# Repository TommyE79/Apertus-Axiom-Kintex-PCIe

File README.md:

# Apertus-Axiom-Kintex-PCIe
 Apertus-Axiom-Kintex-PCIe Bases on SSITLINV-FPGA_Board

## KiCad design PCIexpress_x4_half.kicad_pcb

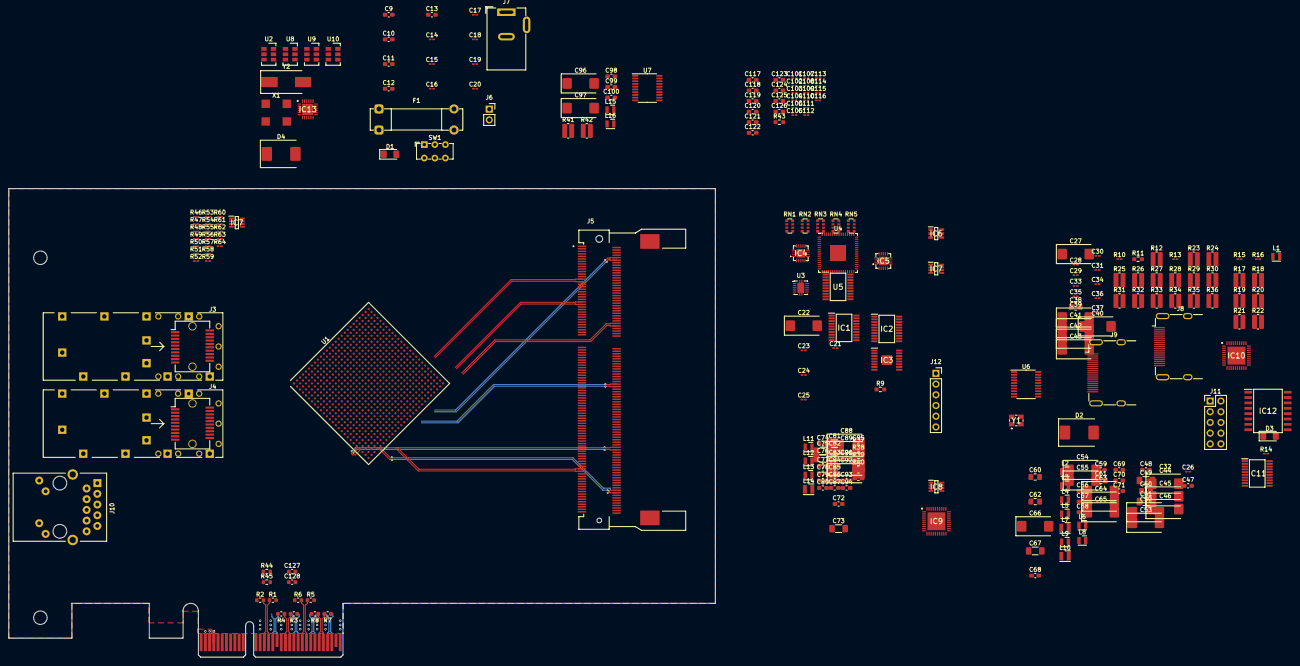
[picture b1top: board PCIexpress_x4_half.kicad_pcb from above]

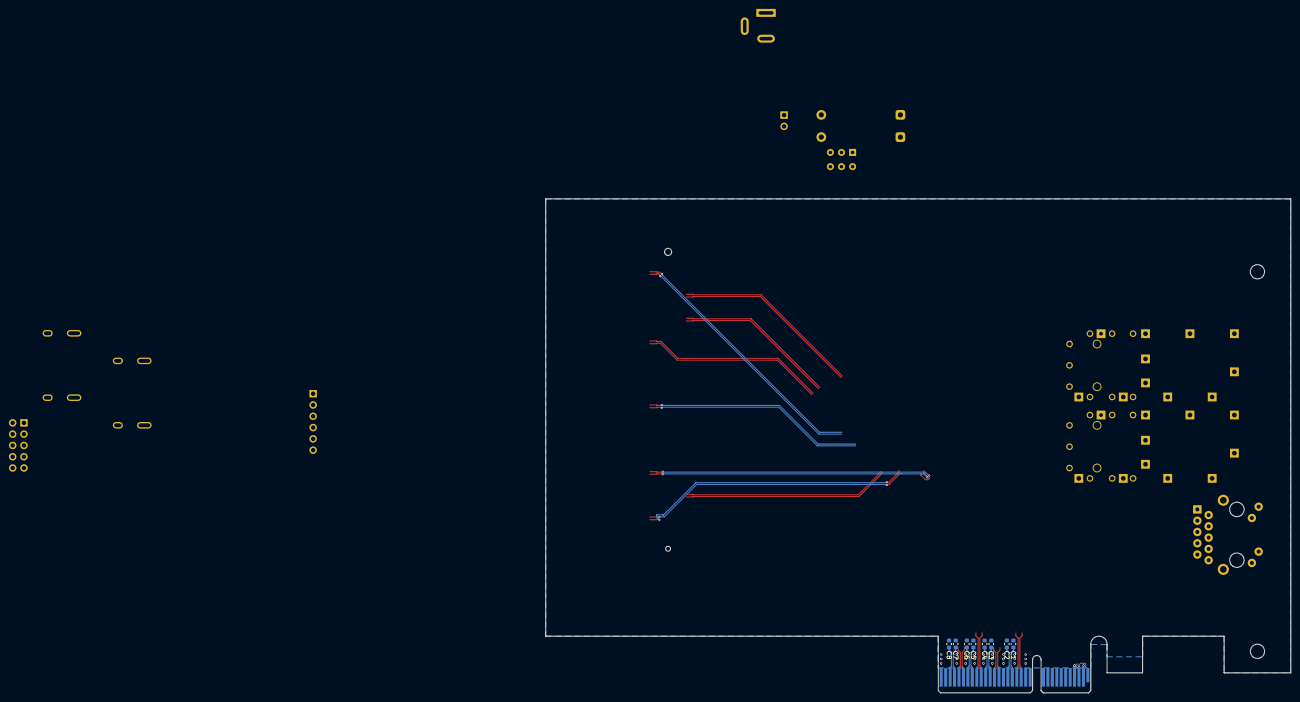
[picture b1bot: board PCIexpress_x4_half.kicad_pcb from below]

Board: 4 copper layers, 167.7 x 111.2 mm, 258 parts (8 on the bottom side), 241 nets.

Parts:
C1, C2, C3, C4, C5, C6, C7, C8, C127, C128: 100n; C_0603_1608Metric
C9, C10, C11, C12, C13, C48, C56, C57, C58, C59, C68, C69, C70, C71, C72, C74, C77, C78, C79, C80, C87, C90, C93, C94, C95, C98, C99, C100, C117, C118, C119, C120, C121, C122, C123, C124, C125, C126: 100n; C_0603_1608Metric_Pad1.08x0.95mm_HandSolder
C14, C15, C16, C17, C18, C19, C20, C21, C23, C24, C25, C26, C28, C29, C30, C31, C32, C33, C34, C35, C36, C37, C101, C102, C103, C104, C105, C106, C107, C108, C109, C110, C111, C112, C113, C114, C115, C116: 100n; C_0201_0603Metric_Pad0.64x0.40mm_HandSolder
C22, C27: 330u; CP_EIA-7343-30_AVX-N_Pad2.25x2.55mm_HandSolder
C38, C50: 100n; C_0805_2012Metric_Pad1.18x1.45mm_HandSolder
C39, C43, C63: 22uF; CP_EIA-7343-40_Kemet-Y_Pad2.25x2.55mm_HandSolder
C40, C41, C42, C44, C45, C46, C64, C65, C66: 22uf; CP_EIA-7343-43_Kemet-X_Pad2.25x2.55mm_HandSolder
C47: 100p; C_0603_1608Metric_Pad1.08x0.95mm_HandSolder
C49, C51: 1u; C_1206_3216Metric_Pad1.33x1.80mm_HandSolder
C52, C53, C54, C55: 330uF; CP_EIA-7343-43_Kemet-X_Pad2.25x2.55mm_HandSolder
C60, C62: 330p; C_0805_2012Metric_Pad1.18x1.45mm_HandSolder
C61: 22p; C_0805_2012Metric_Pad1.18x1.45mm_HandSolder
C67, C73, C75, C81: 10u; C_1206_3216Metric_Pad1.33x1.80mm_HandSolder
C76, C82: 330u; C_1206_3216Metric_Pad1.33x1.80mm_HandSolder
C83, C85: 8200p; C_0603_1608Metric_Pad1.08x0.95mm_HandSolder
C84, C86: 10n; C_0603_1608Metric_Pad1.08x0.95mm_HandSolder
C88, C91: 100u; CP_EIA-7343-43_Kemet-X_Pad2.25x2.55mm_HandSolder
C89, C96: 22u; CP_EIA-7343-43_Kemet-X_Pad2.25x2.55mm_HandSolder
C92: 330u; CP_EIA-7343-43_Kemet-X_Pad2.25x2.55mm_HandSolder
C97: 330u; CP_EIA-7343-31_Kemet-D_Pad2.25x2.55mm_HandSolder
D1, D3: LED; LED_1206_3216Metric_Pad1.42x1.75mm_HandSolder
D2, D4: B340; D_SMC
F1: Fuse; Fuseholder_Clip-5x20mm_Bel_FC-203-22_Lateral_P17.80x5.00mm_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
IC1, IC2, IC11: TXS0108EPWRG4; SOP65P640X120-20N
IC3: TPS40057PWP; SOP65P640X120-17N
IC4, IC5: TPS54620RHLR; TPS54622RHLR
IC6: MP2359DJ-LF-Z; SOT95P280X100-6N
IC7, IC7#2, IC8: MP2315SGJ-Z; SOT65P280X100-8N
IC9, IC10: TMDS141RHAR; QFN50P600X600X100-41N-D
IC12: S25FL256LAGMFI001; SOIC127P1030X265-16N
IC13: SI5338A-B04911-GM; QFN50P400X400X90-25N-D
J1: PCIexpress_x4
J2: PCIexpress_bracket; PCIexpress_bracket_full
J3, J4: SFP+; Connector_SFP_and_Cage
J5: 2-2013289-2; TE_2-2013289-2
J6: FAN; PinSocket_1x02_P2.54mm_Vertical
J7: Jack-DC; BarrelJack_Wuerth_6941xx301002
J8, J9: HDMI_A_1.4; HDMI_A_Molex_208658-1001_Horizontal
J10: RJ45_RB1-125B8G1A; RJ45_UDE_RB1-125B8G1A
J11: Conn_02x05_Odd_Even; PinHeader_2x05_P2.54mm_Vertical
J12: Conn_01x06_Socket; PinSocket_1x06_P2.54mm_Vertical
L1, L2: 100n; L_Wurth_WE-LQSH-2010
L3, L4, L5, L6: L; L_Wurth_WE-LQSH-2010
L7: 1u5; L_Wurth_WE-LQSH-2512
L8, L9, L11, L12, L13, L15, L16: 100nH; L_Wurth_WE-LQSH-2010
L10, L14: 3u3; L_Wurth_WE-LQSH-2512
R1, R2, R3, R4, R5, R6, R7, R8, R44, R45: 49.9; R_0603_1608Metric
R9, R43: 49R9; R_0603_1608Metric_Pad0.98x0.95mm_HandSolder
R10: 49R9; R_0201_0603Metric_Pad0.64x0.40mm_HandSolder
R11: 4k7; R_0603_1608Metric_Pad0.98x0.95mm_HandSolder
R12, R37, R41: R; R_0612_1632Metric_Pad1.18x3.40mm_HandSolder
R13, R14, R15, R16: 4k7; R_0201_0603Metric_Pad0.64x0.40mm_HandSolder
R17: 20k; R_0612_1632Metric_Pad1.18x3.40mm_HandSolder
R18: 59k; R_0612_1632Metric_Pad1.18x3.40mm_HandSolder
R19: 120k; R_0612_1632Metric_Pad1.18x3.40mm_HandSolder
R20: 1k; R_0612_1632Metric_Pad1.18x3.40mm_HandSolder
R21, R22, R35, R39: 100k; R_0612_1632Metric_Pad1.18x3.40mm_HandSolder
R23: 10k; R_0612_1632Metric_Pad1.18x3.40mm_HandSolder
R24: 43k2; R_0612_1632Metric_Pad1.18x3.40mm_HandSolder
R25, R26, R27, R28: 4k7; R_0612_1632Metric_Pad1.18x3.40mm_HandSolder
R29, R32: 1k69; R_0612_1632Metric_Pad1.18x3.40mm_HandSolder
R30, R33: 24k; R_0612_1632Metric_Pad1.18x3.40mm_HandSolder
R31, R34: 22k; R_0612_1632Metric_Pad1.18x3.40mm_HandSolder
R36, R40: 35k7; R_0612_1632Metric_Pad1.18x3.40mm_HandSolder
R38, R42: 8k06; R_0612_1632Metric_Pad1.18x3.40mm_HandSolder
R46: 27k; R_0201_0603Metric_Pad0.64x0.40mm_HandSolder
R47: 60k4; R_0201_0603Metric_Pad0.64x0.40mm_HandSolder
R48, R55: 40k2; R_0201_0603Metric_Pad0.64x0.40mm_HandSolder
R49: 49k9; R_0201_0603Metric_Pad0.64x0.40mm_HandSolder
R50, R52, R64: 100k; R_0201_0603Metric_Pad0.64x0.40mm_HandSolder
R51, R62: 10R; R_0201_0603Metric_Pad0.64x0.40mm_HandSolder
R53: 59k; R_0201_0603Metric_Pad0.64x0.40mm_HandSolder
R54, R63: 0R; R_0201_0603Metric_Pad0.64x0.40mm_HandSolder
R56: 31k6; R_0201_0603Metric_Pad0.64x0.40mm_HandSolder
R57: 53k6; R_0201_0603Metric_Pad0.64x0.40mm_HandSolder
R58: 47k; R_0201_0603Metric_Pad0.64x0.40mm_HandSolder
R59: 75k; R_0201_0603Metric_Pad0.64x0.40mm_HandSolder
R60: 20k5; R_0201_0603Metric_Pad0.64x0.40mm_HandSolder
R61: 39k2; R_0201_0603Metric_Pad0.64x0.40mm_HandSolder
RN1, RN2, RN3, RN4, RN5: R_Pack04; R_Array_Convex_4x0612
SW1: SW_SPDT; SW_E-Switch_EG1271_SPDT
U1: XC7K325T-FFG676; Xilinx_FFG676
U2, U8, U9, U10: XUX53; Oscillator_SMD_IDT_JS6-6_5.0x3.2mm_P1.27mm
U3: TPS51200DRC; VSON-10-1EP_3x3mm_P0.5mm_EP1.65x2.4mm
U4: RTL8211EG-VB-CG; QFN-64-1EP_9x9mm_P0.5mm_EP3.8x3.8mm
U5: SN74LV245ATPWR; SOP65P640X120-20N
U6, U7: TXS0108EPW; TSSOP-20_4.4x6.5mm_P0.65mm
X1: XO91; Oscillator_SMD_EuroQuartz_XO91-4Pin_7.0x5.0mm
Y1: X32-25.000-12-30_30_4085; X32250001230304085
Y2: 25M; Crystal_SMD_EuroQuartz_MQ2-2Pin_7.0x5.0mm_HandSoldering

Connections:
+3.3V: J5.199, L8.1, R11.2
+3V3: J1.A9 (+3.3V), J1.A10 (+3.3V), J1.B8 (+3.3V)
+12V: C9.2, C10.2, C11.1, C12.2, C13.2, C14.2, C15.2, C16.2, C17.2, C18.2, C19.2, C20.2, C21.2, C22.2, C23.2, C24.2, C25.2, C26.2, C27.2, C28.2, C29.2, C30.2, C31.2, C32.2, C33.2, C34.2, C35.2, C36.2, C37.2, C38.1, C38.2, C39.1, C39.2, C40.1, C40.2, C41.1, C41.2, C42.1, C42.2, C43.1, C43.2, C44.1, C44.2, C45.1, C45.2, C46.1, C46.2, C47.1, C49.1, C50.1, C52.2, C53.2, C54.2, C55.2, C56.2, C57.2, C58.2, C59.2, C63.2, C64.2, C65.2, C66.2, C67.1, C68.1, C71.1, C83.2, C84.2, C85.2, C86.2, C88.2, C89.1, C89.2, C91.2, C92.2, C93.2, C94.2, C95.2, C96.1, C96.2, C97.2, C98.2, C99.2, C100.2, C101.2, C102.2, C103.2, C104.2, C105.2, C106.2, C107.2, C108.2, C109.2, C110.2, C111.2, C112.2, C113.2, C114.2, C115.2, C116.2, C117.2, C118.2, C119.2, C120.2, C121.2, C122.2, C123.2, C124.2, C125.2, C126.2, F1.2, IC3.5 (SGND), IC3.15 (VIN), IC3.17 (EP), IC4.2 (GND_1), IC4.3 (GND_2), IC4.4 (PVIN_1), IC4.5 (PVIN_2), IC4.6 (VIN), IC4.15 (EP), IC5.2 (GND_1), IC5.3 (GND_2), IC5.4 (PVIN_1), IC5.5 (PVIN_2), IC5.6 (VIN), IC5.15 (EP), IC6.2 (GND), IC7#2.2 (IN), IC7#2.4 (GND), IC8.2 (IN), IC8.4 (GND), J1.A2 (+12V), J1.A3 (+12V), J1.A4 (GND), J1.A12 (GND), J1.A15 (GND), J1.A18 (GND), J1.A20 (GND), J1.A23 (GND), J1.A24 (GND), J1.A27 (GND), J1.A28 (GND), J1.A31 (GND), J1.B1 (+12V), J1.B2 (+12V), J1.B3 (+12V), J1.B4 (GND), J1.B7 (GND), J1.B13 (GND), J1.B16 (GND), J1.B18 (GND), J1.B21 (GND), J1.B22 (GND), J1.B25 (GND), J1.B26 (GND), J1.B29 (GND), J1.B32 (GND), J5.2, J5.3, J5.8, J5.9, J5.13, J5.14, J5.19, J5.20, J5.25, J5.26, J5.31, J5.32, J5.37, J5.38, J5.43, J5.44, J5.48, J5.49, J5.54, J5.55, J5.60, J5.61, J5.65, J5.66, J5.71, J5.72, J5.127, J5.128, J5.133, J5.134, J5.138, J5.139, J5.144, J5.145, J5.150, J5.151, J5.155, J5.156, J5.161, J5.162, J5.167, J5.168, J5.172, J5.173, J5.178, J5.179, J5.184, J5.185, J5.189, J5.190, J5.195, J5.196, J5.197, J5.201, J5.203, J5.204, J5.SH1 (SHIELD), J5.SH2 (SHIELD__1), J6.1, J6.2, J7.2, J7.3, R1.2, R2.2, R3.2, R4.2, R5.2, R6.2, R7.2, R8.2, R10.2, R14.1, R15.1, R16.1, R17.2, R18.1, R19.1, R20.1, R22.1, R26.1, R30.1, R33.1, R35.1, R36.1, R38.2, R39.1, R40.1, R42.2, R44.2, R45.2, R46.2, R47.2, R48.2, R52.1, R56.2, R57.1, R58.1, R61.2, R64.1, U1.A1 (GND), U1.A2 (GND), U1.A5 (GND), U1.A6 (GND), U1.A7 (GND), U1.A16 (GND), U1.A26 (GND), U1.AA6 (GND), U1.AA16 (GND), U1.AA26 (GND), U1.AB3 (GND), U1.AB13 (GND), U1.AB23 (GND), U1.AC10 (GND), U1.AC20 (GND), U1.AD7 (GND), U1.AD17 (GND), U1.AE4 (GND), U1.AE14 (GND), U1.AE24 (GND), U1.AF1 (GND), U1.AF11 (GND), U1.AF21 (GND), U1.B4 (GND), U1.B7 (GND), U1.B13 (GND), U1.B23 (GND), U1.C1 (GND), U1.C5 (GND), U1.C7 (GND), U1.C10 (GND), U1.C20 (GND), U1.D4 (GND), U1.D7 (GND), U1.D17 (GND), U1.E1 (GND), U1.E2 (GND), U1.E5 (GND), U1.E7 (GND), U1.E14 (GND), U1.E24 (GND), U1.F3 (GND), U1.F4 (GND), U1.F7 (GND), U1.F11 (GND), U1.F21 (GND), U1.G1 (GND), U1.G5 (GND), U1.G8 (GND), U1.G18 (GND), U1.H4 (GND), U1.H7 (GND), U1.H15 (GND), U1.H25 (GND), U1.J1 (GND), U1.J2 (GND), U1.J5 (GND), U1.J12 (GND), U1.J22 (GND), U1.K3 (GND), U1.K4 (GND), U1.K7 (GND), U1.K9 (GND), U1.K11 (GND), U1.K13 (GND), U1.K19 (GND), U1.L1 (GND), U1.L5 (GND), U1.L10 (GND), U1.L12 (GND), U1.L14 (GND), U1.L16 (GND), U1.L26 (GND), U1.M4 (GND), U1.M7 (GND), U1.M9 (GND), U1.M13 (GND), U1.M15 (GND), U1.M23 (GND), U1.N1 (GND), U1.N2 (GND), U1.N5 (GND), U1.N7 (GND), U1.N10 (GND), U1.N14 (GND), U1.N20 (GND), U1.P3 (GND), U1.P4 (GND), U1.P9 (GND), U1.P13 (GND), U1.P15 (GND), U1.P17 (GND), U1.R1 (GND), U1.R2 (GND), U1.R5 (GND), U1.R8 (GND), U1.R10 (GND), U1.R14 (GND), U1.R24 (GND), U1.T1 (GND), U1.T3 (GND), U1.T4 (GND), U1.T9 (GND), U1.T11 (GND), U1.T13 (GND), U1.T15 (GND), U1.T21 (GND), U1.U8 (GND), U1.U10 (GND), U1.U12 (GND), U1.U14 (GND), U1.U18 (GND), U1.V5 (GND), U1.V15 (GND), U1.V25 (GND), U1.W2 (GND), U1.W12 (GND), U1.W22 (GND), U1.Y9 (GND), U1.Y19 (GND), U3.4 (GND), U3.8 (GND), U3.11 (GND)
/FPGA - kintex/Bank-B/VCCIO: U1.A21 (VCCO_14), U1.B18 (VCCO_15), U1.C25 (VCCO_14), U1.D22 (VCCO_14), U1.E19 (VCCO_15), U1.F16 (VCCO_15), U1.F26 (VCCO_14), U1.G23 (VCCO_14), U1.H20 (VCCO_15), U1.J17 (VCCO_15), U1.L21 (VCCO_14), U1.M18 (VCCO_15)
/FPGA - kintex/Bank-C/0V75-VREF2: C9.1, C10.1, L1.2, U1.AE16 (IO_L6N_T0_VREF_32), U1.Y18 (IO_L19N_T3_VREF_32)
/FPGA - kintex/Bank-C/DDR1V5: U1.AB18 (VCCO_32), U1.AC15 (VCCO_32), U1.AE19 (VCCO_32), U1.AF16 (VCCO_32), U1.W17 (VCCO_32), U1.Y14 (VCCO_32)
/FPGA - kintex/Bank-C/DDR3-B-EVENT: J5.198, U1.V7 (IO_L2N_T0_33)
/FPGA - kintex/Bank-C/DDR3-B_BA0: J5.109, U1.AE8 (IO_L22P_T3_33)
/FPGA - kintex/Bank-C/DDR3-B_BA1: J5.108, U1.AA7 (IO_L8N_T1_33)
/FPGA - kintex/Bank-C/DDR3-B_BA2: J5.79, U1.AF13 (IO_L23N_T3_33)
/FPGA - kintex/Bank-C/DDR3-B_CKE0: J5.73, U1.AB10 (IO_L14N_T2_SRCC_33)
/FPGA - kintex/Bank-C/DDR3-B_CKE1: J5.74, U1.AA10 (IO_L14P_T2_SRCC_33)
/FPGA - kintex/Bank-C/DDR3-B_CLK0+: J5.101, U1.AC9 (IO_L12P_T1_MRCC_33)
/FPGA - kintex/Bank-C/DDR3-B_CLK0-: J5.103, U1.AD9 (IO_L12N_T1_MRCC_33)
/FPGA - kintex/Bank-C/DDR3-B_CLK1+: J5.102, U1.AA9 (IO_L11P_T1_SRCC_33)
/FPGA - kintex/Bank-C/DDR3-B_CLK1-: J5.104, U1.AB9 (IO_L11N_T1_SRCC_33)
/FPGA - kintex/Bank-C/DDR3-B_CS0: J5.114, U1.AA13 (IO_L16P_T2_33)
/FPGA - kintex/Bank-C/DDR3-B_CS1: J5.121, U1.AD13 (IO_L17N_T2_33)
/FPGA - kintex/Bank-C/DDR3-B_DM0: J5.11, U1.AD16 (IO_L6P_T0_32)
/FPGA - kintex/Bank-C/DDR3-B_DM1: J5.28, U1.AB16 (IO_L12P_T1_MRCC_32)
/FPGA - kintex/Bank-C/DDR3-B_DM2: J5.46, U1.AB19 (IO_L18P_T2_32)
/FPGA - kintex/Bank-C/DDR3-B_DM3: J5.63, U1.V17 (IO_L20N_T3_32)
/FPGA - kintex/Bank-C/DDR3-B_DM4: J5.136, U1.U1 (IO_L2N_T0_34)
/FPGA - kintex/Bank-C/DDR3-B_DM5: J5.153, U1.AA3 (IO_L12P_T1_MRCC_34)
/FPGA - kintex/Bank-C/DDR3-B_DM6: J5.170, U1.AD6 (IO_L18P_T2_34)
/FPGA - kintex/Bank-C/DDR3-B_DM7: J5.187, U1.AE1 (IO_L20N_T3_34)
/FPGA - kintex/Bank-C/DDR3-B_DQ0: J5.5, U1.AF17 (IO_L1N_T0_32)
/FPGA - kintex/Bank-C/DDR3-B_DQ1: J5.7, U1.AE17 (IO_L1P_T0_32)
/FPGA - kintex/Bank-C/DDR3-B_DQ2: J5.15, U1.AF15 (IO_L2N_T0_32)
/FPGA - kintex/Bank-C/DDR3-B_DQ3: J5.17, U1.AF14 (IO_L2P_T0_32)
/FPGA - kintex/Bank-C/DDR3-B_DQ4: J5.4, U1.AE15 (IO_L4N_T0_32)
/FPGA - kintex/Bank-C/DDR3-B_DQ5: J5.6, U1.AD15 (IO_L4P_T0_32)
/FPGA - kintex/Bank-C/DDR3-B_DQ6: J5.16, U1.AF20 (IO_L5N_T0_32)
/FPGA - kintex/Bank-C/DDR3-B_DQ7: J5.18, U1.AF19 (IO_L5P_T0_32)
/FPGA - kintex/Bank-C/DDR3-B_DQ8: J5.21, U1.AA15 (IO_L7N_T1_32)
/FPGA - kintex/Bank-C/DDR3-B_DQ9: J5.23, U1.AA14 (IO_L7P_T1_32)
/FPGA - kintex/Bank-C/DDR3-B_DQ10: J5.33, U1.AC14 (IO_L8P_T1_32)
/FPGA - kintex/Bank-C/DDR3-B_DQ11: J5.35, U1.AD14 (IO_L8N_T1_32)
/FPGA - kintex/Bank-C/DDR3-B_DQ12: J5.22, U1.AB14 (IO_L10P_T1_32)
/FPGA - kintex/Bank-C/DDR3-B_DQ13: J5.24, U1.AB15 (IO_L10N_T1_32)
/FPGA - kintex/Bank-C/DDR3-B_DQ14: J5.34, U1.AA18 (IO_L11N_T1_SRCC_32)
/FPGA - kintex/Bank-C/DDR3-B_DQ15: J5.36, U1.AA17 (IO_L11P_T1_SRCC_32)
/FPGA - kintex/Bank-C/DDR3-B_DQ16: J5.39, U1.AC18 (IO_L13P_T2_MRCC_32)
/FPGA - kintex/Bank-C/DDR3-B_DQ17: J5.41, U1.AD18 (IO_L13N_T2_MRCC_32)
/FPGA - kintex/Bank-C/DDR3-B_DQ18: J5.51, U1.AC17 (IO_L14N_T2_SRCC_32)
/FPGA - kintex/Bank-C/DDR3-B_DQ19: J5.53, U1.AB17 (IO_L14P_T2_SRCC_32)
/FPGA - kintex/Bank-C/DDR3-B_DQ20: J5.40, U1.AA20 (IO_L16N_T2_32)
/FPGA - kintex/Bank-C/DDR3-B_DQ21: J5.42, U1.AA19 (IO_L16P_T2_32)
/FPGA - kintex/Bank-C/DDR3-B_DQ22: J5.50, U1.AD19 (IO_L17N_T2_32)
/FPGA - kintex/Bank-C/DDR3-B_DQ23: J5.52, U1.AC19 (IO_L17P_T2_32)
/FPGA - kintex/Bank-C/DDR3-B_DQ24: J5.57, U1.W14 (IO_L24N_T3_32)
/FPGA - kintex/Bank-C/DDR3-B_DQ25: J5.59, U1.V14 (IO_L24P_T3_32)
/FPGA - kintex/Bank-C/DDR3-B_DQ26: J5.67, U1.V19 (IO_L23N_T3_32)
/FPGA - kintex/Bank-C/DDR3-B_DQ27: J5.69, U1.V18 (IO_L23P_T3_32)
/FPGA - kintex/Bank-C/DDR3-B_DQ28: J5.56, U1.V16 (IO_L20P_T3_32)
/FPGA - kintex/Bank-C/DDR3-B_DQ29: J5.58, U1.W15 (IO_L22P_T3_32)
/FPGA - kintex/Bank-C/DDR3-B_DQ30: J5.68, U1.W16 (IO_L22N_T3_32)
/FPGA - kintex/Bank-C/DDR3-B_DQ31: J5.70, U1.Y17 (IO_L19P_T3_32)
/FPGA - kintex/Bank-C/DDR3-B_DQ32: J5.129, U1.V4 (IO_L6P_T0_34)
/FPGA - kintex/Bank-C/DDR3-B_DQ33: J5.131, U1.U6 (IO_L1P_T0_34)
/FPGA - kintex/Bank-C/DDR3-B_DQ34: J5.141, U1.U5 (IO_L1N_T0_34)
/FPGA - kintex/Bank-C/DDR3-B_DQ35: J5.143, U1.U2 (IO_L2P_T0_34)
/FPGA - kintex/Bank-C/DDR3-B_DQ36: J5.130, U1.V3 (IO_L4P_T0_34)
/FPGA - kintex/Bank-C/DDR3-B_DQ37: J5.132, U1.W3 (IO_L4N_T0_34)
/FPGA - kintex/Bank-C/DDR3-B_DQ38: J5.140, U1.U7 (IO_L5P_T0_34)
/FPGA - kintex/Bank-C/DDR3-B_DQ39: J5.142, U1.V6 (IO_L5N_T0_34)
/FPGA - kintex/Bank-C/DDR3-B_DQ40: J5.147, U1.Y3 (IO_L7P_T1_34)
/FPGA - kintex/Bank-C/DDR3-B_DQ41: J5.149, U1.Y2 (IO_L7N_T1_34)
/FPGA - kintex/Bank-C/DDR3-B_DQ42: J5.157, U1.V2 (IO_L8P_T1_34)
/FPGA - kintex/Bank-C/DDR3-B_DQ43: J5.159, U1.V1 (IO_L8N_T1_34)
/FPGA - kintex/Bank-C/DDR3-B_DQ44: J5.146, U1.W1 (IO_L10P_T1_34)
/FPGA - kintex/Bank-C/DDR3-B_DQ45: J5.148, U1.Y1 (IO_L10N_T1_34)
/FPGA - kintex/Bank-C/DDR3-B_DQ46: J5.158, U1.AB2 (IO_L11P_T1_SRCC_34)
/FPGA - kintex/Bank-C/DDR3-B_DQ47: J5.160, U1.AC2 (IO_L11N_T1_SRCC_34)
/FPGA - kintex/Bank-C/DDR3-B_DQ48: J5.163, U1.AA4 (IO_L13P_T2_MRCC_34)
/FPGA - kintex/Bank-C/DDR3-B_DQ49: J5.165, U1.AB4 (IO_L13N_T2_MRCC_34)
/FPGA - kintex/Bank-C/DDR3-B_DQ50: J5.175, U1.AC4 (IO_L14P_T2_SRCC_34)
/FPGA - kintex/Bank-C/DDR3-B_DQ51: J5.177, U1.AC3 (IO_L14N_T2_SRCC_34)
/FPGA - kintex/Bank-C/DDR3-B_DQ52: J5.164, U1.AC6 (IO_L16N_T2_34)
/FPGA - kintex/Bank-C/DDR3-B_DQ53: J5.166, U1.AB6 (IO_L16P_T2_34)
/FPGA - kintex/Bank-C/DDR3-B_DQ54: J5.174, U1.Y6 (IO_L17P_T2_34)
/FPGA - kintex/Bank-C/DDR3-B_DQ55: J5.176, U1.Y5 (IO_L17N_T2_34)
/FPGA - kintex/Bank-C/DDR3-B_DQ56: J5.181, U1.AD4 (IO_L19P_T3_34)
/FPGA - kintex/Bank-C/DDR3-B_DQ57: J5.183, U1.AD1 (IO_L20P_T3_34)
/FPGA - kintex/Bank-C/DDR3-B_DQ58: J5.191, U1.AF2 (IO_L24N_T3_34)
/FPGA - kintex/Bank-C/DDR3-B_DQ59: J5.193, U1.AE2 (IO_L22N_T3_34)
/FPGA - kintex/Bank-C/DDR3-B_DQ60: J5.180, U1.AE6 (IO_L23P_T3_34)
/FPGA - kintex/Bank-C/DDR3-B_DQ61: J5.182, U1.AE5 (IO_L23N_T3_34)
/FPGA - kintex/Bank-C/DDR3-B_DQ62: J5.192, U1.AF3 (IO_L24P_T3_34)
/FPGA - kintex/Bank-C/DDR3-B_DQ63: J5.194, U1.AE3 (IO_L22P_T3_34)
/FPGA - kintex/Bank-C/DDR3-B_DQS0+: J5.12, U1.AE18 (IO_L3P_T0_DQS_32)
/FPGA - kintex/Bank-C/DDR3-B_DQS0-: J5.10, U1.AF18 (IO_L3N_T0_DQS_32)
/FPGA - kintex/Bank-C/DDR3-B_DQS1+: J5.29, U1.Y15 (IO_L9P_T1_DQS_32)
/FPGA - kintex/Bank-C/DDR3-B_DQS1-: J5.27, U1.Y16 (IO_L9N_T1_DQS_32)
/FPGA - kintex/Bank-C/DDR3-B_DQS2+: J5.47, U1.AD20 (IO_L15P_T2_DQS_32)
/FPGA - kintex/Bank-C/DDR3-B_DQS2-: J5.45, U1.AE20 (IO_L15N_T2_DQS_32)
/FPGA - kintex/Bank-C/DDR3-B_DQS3+: J5.64, U1.W18 (IO_L21P_T3_DQS_32)
/FPGA - kintex/Bank-C/DDR3-B_DQS3-: J5.62, U1.W19 (IO_L21N_T3_DQS_32)
/FPGA - kintex/Bank-C/DDR3-B_DQS4+: J5.137, U1.W6 (IO_L3P_T0_DQS_34)
/FPGA - kintex/Bank-C/DDR3-B_DQS4-: J5.135, U1.W5 (IO_L3N_T0_DQS_34)
/FPGA - kintex/Bank-C/DDR3-B_DQS5+: J5.154, U1.AB1 (IO_L9P_T1_DQS_34)
/FPGA - kintex/Bank-C/DDR3-B_DQS5-: J5.152, U1.AC1 (IO_L9N_T1_DQS_34)
/FPGA - kintex/Bank-C/DDR3-B_DQS6+: J5.171, U1.AA5 (IO_L15P_T2_DQS_34)
/FPGA - kintex/Bank-C/DDR3-B_DQS6-: J5.169, U1.AB5 (IO_L15N_T2_DQS_34)
/FPGA - kintex/Bank-C/DDR3-B_DQS7+: J5.188, U1.AF5 (IO_L21P_T3_DQS_34)
/FPGA - kintex/Bank-C/DDR3-B_DQS7-: J5.186, U1.AF4 (IO_L21N_T3_DQS_34)
/FPGA - kintex/Bank-C/DDR3-B_ODT0: J5.116, U1.AA12 (IO_L16N_T2_33)
/FPGA - kintex/Bank-C/DDR3-B_ODT1: J5.120, U1.Y13 (IO_L18P_T2_33)
/FPGA - kintex/Bank-C/DDR3-B_RAS: J5.110, U1.Y7 (IO_L4N_T0_33)
/FPGA - kintex/Bank-C/DDR3-B_RESET: J5.30, U1.AB20 (IO_L18N_T2_32)
/FPGA - kintex/Bank-C/DDR3-B_SCL: J5.202, U1.W8 (IO_L6N_T0_VREF_33)
/FPGA - kintex/Bank-C/DDR3-B_SDA: J5.200, U1.V8 (IO_L2P_T0_33)
/FPGA - kintex/Bank-C/DDR3-B_WE: J5.113, U1.AF8 (IO_L22N_T3_33)
/FPGA - kintex/Bank-D/0V75-VREF1: C12.1, C13.1, L2.2, U1.AD3 (IO_L19N_T3_VREF_34), U1.W4 (IO_L6N_T0_VREF_34)
/FPGA - kintex/Bank-D/DDR1V5: R9.1, U1.AA1 (VCCO_34), U1.AA11 (VCCO_33), U1.AB8 (VCCO_33), U1.AC5 (VCCO_34), U1.AD2 (VCCO_34), U1.AD12 (VCCO_33), U1.AE9 (VCCO_33), U1.AF6 (VCCO_34), U1.U3 (VCCO_34), U1.V10 (VCCO_33), U1.W7 (VCCO_33), U1.Y4 (VCCO_34)
/FPGA - kintex/Bank-E/PCIE_CLK+: C127.2, U1.H6 (MGTREFCLK0P_115)
/FPGA - kintex/Bank-E/PCIE_CLK-: C128.1, U1.H5 (MGTREFCLK0N_115)
/FPGA - kintex/Bank-F/AVTT1V2: C123.1, C124.1, C125.1, C126.1, R43.2, U1.B3 (MGTAVTT), U1.C2 (MGTAVTT), U1.D3 (MGTAVTT), U1.G2 (MGTAVTT), U1.H3 (MGTAVTT), U1.L2 (MGTAVTT), U1.M3 (MGTAVTT), U1.M5 (MGTAVTTRCAL_115)
/FPGA - kintex/Bank-F/VCCINT1V: C101.1, C102.1, C103.1, C104.1, C105.1, C106.1, C107.1, C108.1, C109.1, C110.1, C111.1, C112.1, C113.1, C114.1, C115.1, C116.1, U1.C6 (MGTAVCC), U1.E6 (MGTAVCC), U1.G6 (MGTAVCC), U1.J6 (MGTAVCC), U1.L6 (MGTAVCC)
/FPGA - kintex/Bank-H/1V8: C117.1, C118.1, C119.1, C120.1, C121.1, C122.1, U1.E8 (VCCBATT_0), U1.L11 (VCCAUX), U1.M10 (VCCAUX), U1.M11 (GNDADC_0), U1.M12 (VCCADC_0), U1.P8 (VCCAUX_IO_G0), U1.P10 (VCCAUX), U1.R9 (VCCAUX_IO_G0), U1.T8 (VCCAUX_IO_G0), U1.T10 (VCCAUX), U1.U11 (VCCAUX)
/FPGA - kintex/Bank-H/VCCINT1V: U1.N13 (VCCBRAM), U1.R13 (VCCBRAM), U1.T12 (VCCBRAM), U1.U13 (VCCBRAM)
/FPGA - kintex/Bank-a/VCCIO: U1.AA21 (VCCO_12), U1.AC25 (VCCO_12), U1.AD22 (VCCO_12), U1.AF26 (VCCO_12), U1.K24 (VCCO_13), U1.N25 (VCCO_13), U1.P22 (VCCO_13), U1.R19 (VCCO_13), U1.T16 (VCCO_13), U1.T26 (VCCO_13), U1.U23 (VCCO_12), U1.V20 (VCCO_12), U1.Y24 (VCCO_12)
/FPGA - kintex/DDR3-B_A0: J5.98, U1.AB7 (IO_L10P_T1_33)
/FPGA - kintex/DDR3-B_A1: J5.97, U1.AD11 (IO_L19P_T3_33)
/FPGA - kintex/DDR3-B_A2: J5.96, U1.AA8 (IO_L8P_T1_33)
/FPGA - kintex/DDR3-B_A3: J5.95, U1.AF10 (IO_L24P_T3_33)
/FPGA - kintex/DDR3-B_A4: J5.92, U1.AC7 (IO_L10N_T1_33)
/FPGA - kintex/DDR3-B_A5: J5.91, U1.AE11 (IO_L19N_T3_VREF_33)
/FPGA - kintex/DDR3-B_A6: J5.90, U1.AC8 (IO_L9P_T1_DQS_33)
/FPGA - kintex/DDR3-B_A7: J5.86, U1.AD8 (IO_L9N_T1_DQS_33)
/FPGA - kintex/DDR3-B_A8: J5.89, U1.AC13 (IO_L17P_T2_33)
/FPGA - kintex/DDR3-B_A9: J5.85, U1.AF12 (IO_L21N_T3_DQS_33)
/FPGA - kintex/DDR3-B_A10: J5.107, U1.AF9 (IO_L24N_T3_33)
/FPGA - kintex/DDR3-B_A11: J5.84, U1.AD10 (IO_L20P_T3_33)
/FPGA - kintex/DDR3-B_A12: J5.83, U1.AE13 (IO_L23P_T3_33)
/FPGA - kintex/DDR3-B_A13: J5.119, U1.AF7 (IO_L7N_T1_33)
/FPGA - kintex/DDR3-B_A14: J5.80, U1.AB12 (IO_L15P_T2_DQS_33)
/FPGA - kintex/DDR3-B_A15: J5.78, U1.AC12 (IO_L15N_T2_DQS_33)
/FPGA - kintex/DDR3-SODIMM/0.75V: C27.1, C28.1, C29.1, C30.1, C31.1, L3.1, L4.1
/FPGA - kintex/DDR3-SODIMM/DDR1V5: L5.1, L6.1, R13.1
/FPGA - kintex/DDR3-SODIMM/SODIMM1V5: C14.1, C15.1, C16.1, C17.1, C18.1, C19.1, C22.1, C23.1, C24.1, C25.1, C26.1, C32.1, C33.1, C34.1, C35.1, C36.1, C37.1, J5.75, J5.76, J5.81, J5.82, J5.87, J5.88, J5.93, J5.94, J5.99, J5.100, J5.105, J5.106, J5.111, J5.112, J5.117, J5.118, J5.123, J5.124, L5.2, L6.2
/FPGA - kintex/DDR3-SODIMM/VREFCA: C21.1, J5.126, L4.2
/FPGA - kintex/DDR3-SODIMM/VREFDQ: C20.1, J5.1, L3.2
/PCIE_RX_0+: C1.1, U1.B6 (MGTXRXP3_116)
/PCIE_RX_0-: C2.2, U1.B5 (MGTXRXN3_116)
/PCIE_RX_1+: C3.1, U1.C4 (MGTXRXP2_116)
/PCIE_RX_1-: C4.2, U1.C3 (MGTXRXN2_116)
/PCIE_RX_2+: C5.1, U1.E4 (MGTXRXP1_116)
/PCIE_RX_2-: C6.2, U1.E3 (MGTXRXN1_116)
/PCIE_RX_3+: C7.1, U1.G4 (MGTXRXP0_116)
/PCIE_RX_3-: C8.2, U1.G3 (MGTXRXN0_116)
/PCIE_TX_0+: R2.1, U1.A4 (MGTXTXP3_116)
/PCIE_TX_0-: R1.1, U1.A3 (MGTXTXN3_116)
/PCIE_TX_1+: R4.1, U1.B2 (MGTXTXP2_116)
/PCIE_TX_1-: R3.1, U1.B1 (MGTXTXN2_116)
/PCIE_TX_2+: R6.1, U1.D2 (MGTXTXP1_116)
/PCIE_TX_2-: R5.1, U1.D1 (MGTXTXN1_116)
/PCIE_TX_3+: R8.1, U1.F2 (MGTXTXP0_116)
/PCIE_TX_3-: R7.1, U1.F1 (MGTXTXN0_116)
/PCIexpress_connector/_PER0_N: C2.1, J1.A17 (PERn0)
/PCIexpress_connector/_PER0_P: C1.2, J1.A16 (PERp0)
/PCIexpress_connector/_PER1_N: C4.1, J1.A22 (PERn1)
/PCIexpress_connector/_PER1_P: C3.2, J1.A21 (PERp1)
/PCIexpress_connector/_PER2_N: C6.1, J1.A26 (PERn2)
/PCIexpress_connector/_PER2_P: C5.2, J1.A25 (PERp2)
/PCIexpress_connector/_PER3_N: C8.1, J1.A30 (PERn3)
/PCIexpress_connector/_PER3_P: C7.2, J1.A29 (PERp3)
/Power2/0.75V: C79.1, C80.1, C81.1, C82.1, U3.6 (REFOUT)
/Power2/1V5_EN: IC5.10 (EN), R40.2, R42.1
/Power2/3V3_EN: IC4.10 (EN), R36.2, R38.1
/Power2/DDR1V5: C67.2, C68.2, C69.2, C70.2, C92.1, C93.1, C94.1, C95.1, C97.1, C98.1, C99.1, C100.1, L9.1, L11.1, L12.1, L13.1, L15.1, L16.1, R28.1, R31.1, R34.1, R37.1, R41.1, U3.2 (VLDOIN)
/Power/VCCINT1V: C52.1, C53.1, C54.1, C55.1, C56.1, C57.1, C58.1, C59.1, L7.2
/REFCLK+: C127.1, J1.A13 (REFCLK+), R45.1
/REFCLK-: C128.2, J1.A14 (REFCLK-), R44.1
/~PERST: J1.A11 (~PERST), R11.1
/~PRSNT1: J1.A1 (~PRSNT1), J1.B31 (~PRSNT2)
unnamed: C60.2, R21.1
unnamed: C62.1, R23.2
unnamed: C62.2, L7.1, R24.2
unnamed: C72.2, C73.2, C74.2, C75.2, C76.2, C77.2, C78.2, C79.2, C80.2, C81.2, C82.2
unnamed: C83.1, R29.1
unnamed: C85.1, R32.1
unnamed: C88.1, L9.2, L10.2, L11.2, L12.2
unnamed: C91.1, L13.2, L14.2, L15.2, L16.2
unnamed: D4.1 (K), IC6.6 (SW)
unnamed: C48.2, IC3.14 (BOOST)
unnamed: C49.2, IC3.3 (BP5)
unnamed: C51.2, IC3.11 (BP10)
unnamed: C61.2, IC3.8 (COMP), R21.2
unnamed: C47.2, IC3.16 (ILIM), R17.1
unnamed: IC3.1 (KFF), R18.2
unnamed: C51.1, IC3.9 (PGND)
unnamed: IC3.2 (RT), R19.2
unnamed: C50.2, IC3.6 (SS/SD)
unnamed: C48.1, IC3.12 (SW)
unnamed: IC3.4 (SYNC), R20.2
unnamed: C60.1, C61.1, IC3.7 (VFB), R22.2, R23.1, R24.1
unnamed: C87.1, IC4.13 (BOOT)
unnamed: IC4.8 (COMP), R29.2
unnamed: C87.2, IC4.11 (PH_1), IC4.12 (PH_2), L10.1
unnamed: IC4.14 (PWRGD), R37.2
unnamed: IC4.1 (RT/CLK), R35.2
unnamed: C84.1, IC4.9 (SS/TR)
unnamed: IC4.7 (VSENSE), R30.2, R31.2
unnamed: C90.1, IC5.13 (BOOT)
unnamed: IC5.8 (COMP), R32.2
unnamed: C90.2, IC5.11 (PH_1), IC5.12 (PH_2), L14.1
unnamed: IC5.14 (PWRGD), R41.2
unnamed: IC5.1 (RT/CLK), R39.2
unnamed: C86.1, IC5.9 (SS/TR)
unnamed: IC5.7 (VSENSE), R33.2, R34.2
unnamed: IC6.4 (EN), R50.2
unnamed: IC6.3 (FB), R49.2
unnamed: IC6.5 (IN), R50.1
unnamed: IC7#2.1 (AAM), R58.2
unnamed: IC7#2.6 (EN), R64.2
unnamed: IC7#2.8 (FB), R60.1
unnamed: IC7#2.3 (SW), R62.2
unnamed: IC8.1 (AAM), R57.2
unnamed: IC8.6 (EN), R52.2
unnamed: IC8.8 (FB), R55.1
unnamed: IC8.3 (SW), R51.2
unnamed: J3.10 (VeeR), J3.11 (VeeR), J3.14 (VeeR)
unnamed: J3.1 (VeeT), J3.17 (VeeT), J3.20 (VeeT)
unnamed: J4.10 (VeeR), J4.11 (VeeR), J4.14 (VeeR)
unnamed: J4.1 (VeeT), J4.17 (VeeT), J4.20 (VeeT)
unnamed: R48.1, R49.1
unnamed: R53.1, R54.2, R55.2, R56.1
unnamed: R59.1, R60.2, R61.1, R63.2
unnamed: J7.1, SW1.2 (B)
unnamed: C63.1, C64.1, C65.1, C66.1, F1.1, SW1.3 (C)
unnamed: C11.2, R9.2, U1.U9 (IO_0_VRN_33)
unnamed: R10.1, U1.V12 (IO_25_VRP_33)
unnamed: R43.1, U1.M6 (MGTRREF_115)
unnamed: R27.2, U3.7 (EN)
unnamed: R25.1, U3.9 (PGOOD)
unnamed: C71.2, R26.2, R28.2, U3.1 (REFIN)
unnamed: L8.2, R25.2, R27.1, U3.10 (VIN)
unnamed: C72.1, C73.1, C74.1, C75.1, C76.1, C77.1, C78.1, U3.3 (VO)
unnamed: C69.1, C70.1, U3.5 (VOSNS)
unnamed: U4.2 (GND), U4.4 (GND), U4.63 (GND), U4.65 (GND)

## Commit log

2025-01-28 WIP
    WIP - save current state
